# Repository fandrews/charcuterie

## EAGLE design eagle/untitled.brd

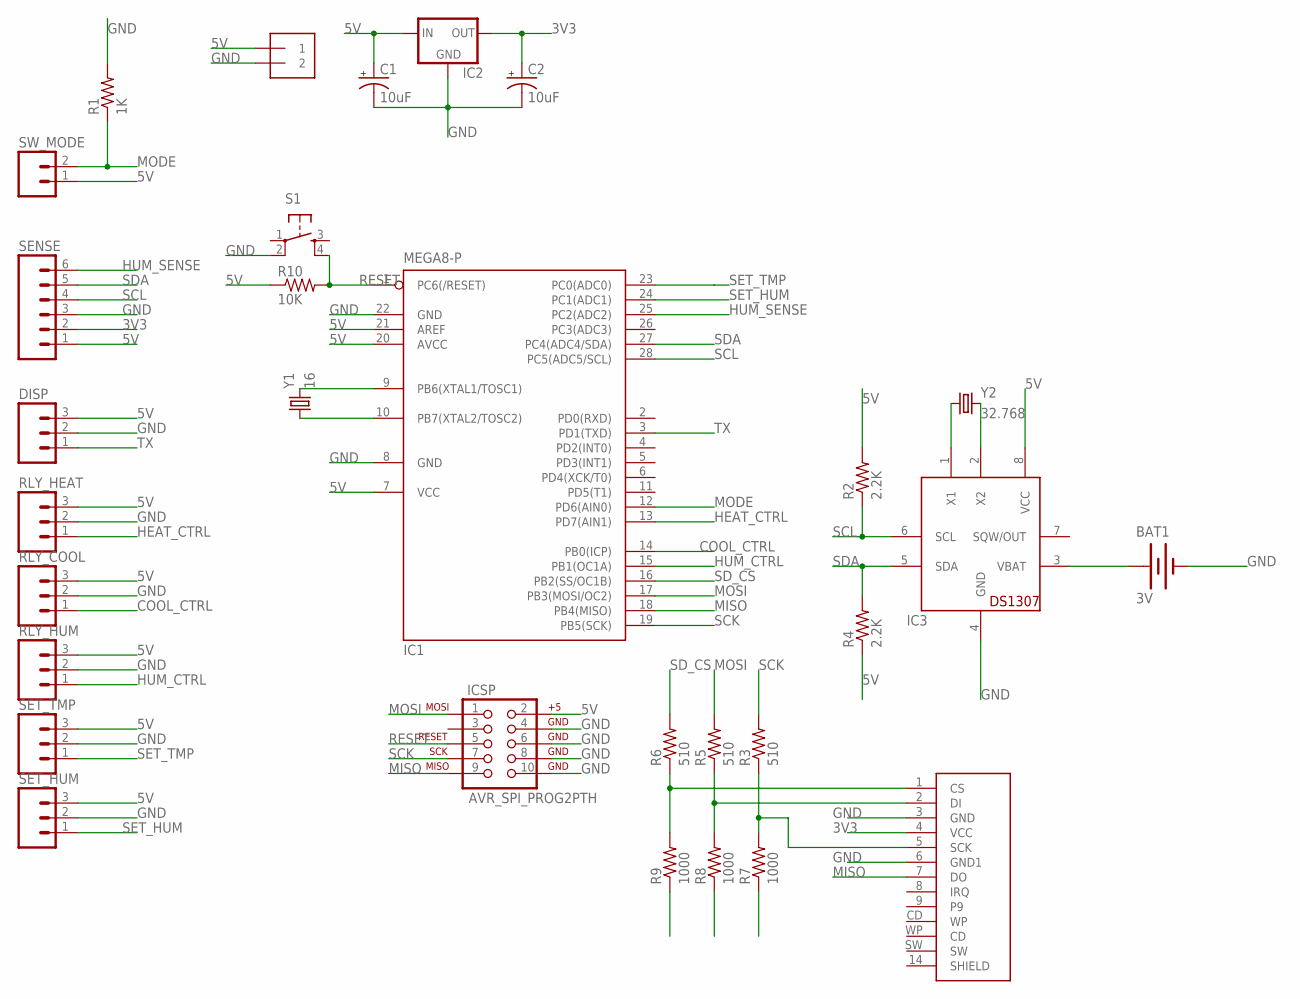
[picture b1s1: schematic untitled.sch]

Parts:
BAT1: 3V; BATTCOM_20MM_PTH
C1, C2: 10uF; CPOL-RADIAL-10UF-25V
DISP: M03PTH; 1X03
IC1: MEGA8-P; DIL28-3
IC2: V_REG_78XX-TO-220; TO-220-ALT
IC3: DS1307; DIL08
ICSP: AVR_SPI_PROG2PTH; AVR_ICSP
PWR_IN: 1X2-3.5MM
R1: 1K; AXIAL-0.3
R2, R4: 2.2K; AXIAL-0.3
R3, R5, R6: 510; AXIAL-0.3
R7, R8, R9: 1000; AXIAL-0.3
R10: 10K; AXIAL-0.3
RLY_COOL: M03PTH; 1X03
RLY_HEAT: M03PTH; 1X03
RLY_HUM: M03PTH; 1X03
S1: TAC_SWITCHPTH; TACTILE-PTH
SD_CARD: SD_CARD_SOCKETSD; SD-MMC_SOCKET-PP
SENSE: M06SIP; 1X06
SET_HUM: M03PTH; 1X03
SET_TMP: M03PTH; 1X03
SW_MODE: M02JST-PTH-2; JST-2-PTH
Y1: 16; HC49U-V
Y2: 32.768; TC26H

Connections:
3V3: C2.1 (+), IC2.OUT, SD_CARD.4 (VCC), SENSE.2
5V: C1.1 (+), DISP.3, IC1.7 (VCC), IC1.20 (AVCC), IC1.21 (AREF), IC2.IN, IC3.8 (VCC), ICSP.2, PWR_IN.1, R2.P$2 (2), R4.P$1 (1), R10.P$1 (1), RLY_COOL.3, RLY_HEAT.3, RLY_HUM.3, SENSE.1, SET_HUM.3, SET_TMP.3, SW_MODE.1
COOL_CTRL: IC1.14 (PB0(ICP)), RLY_COOL.1
GND: BAT1.2 (-), C1.2 (-), C2.2 (-), DISP.2, IC1.8 (GND), IC1.22 (GND), IC2.GND, IC3.4 (GND), ICSP.4, ICSP.6, ICSP.8, ICSP.10, PWR_IN.2, R1.P$2 (2), R7.P$1 (1), R8.P$1 (1), R9.P$1 (1), RLY_COOL.2, RLY_HEAT.2, RLY_HUM.2, S1.2, SD_CARD.3 (GND), SD_CARD.6 (GND1), SENSE.3, SET_HUM.2, SET_TMP.2
HEAT_CTRL: IC1.13 (PD7(AIN1)), RLY_HEAT.1
HUM_CTRL: IC1.15 (PB1(OC1A)), RLY_HUM.1
HUM_SENSE: IC1.25 (PC2(ADC2)), SENSE.6
MISO: IC1.18 (PB4(MISO)), ICSP.9, SD_CARD.7 (DO)
MODE: IC1.12 (PD6(AIN0)), R1.P$1 (1), SW_MODE.2
MOSI: IC1.17 (PB3(MOSI/OC2)), ICSP.1, R5.P$2 (2)
unnamed: IC1.9 (PB6(XTAL1/TOSC1)), Y1.2
unnamed: IC1.10 (PB7(XTAL2/TOSC2)), Y1.1
unnamed: IC3.1 (X1), Y2.1
unnamed: IC3.2 (X2), Y2.2
unnamed: BAT1.1 (+), IC3.3 (VBAT)
unnamed: R6.P$1 (1), R9.P$2 (2), SD_CARD.1 (CS)
unnamed: R5.P$1 (1), R8.P$2 (2), SD_CARD.2 (DI)
unnamed: R3.P$1 (1), R7.P$2 (2), SD_CARD.5 (SCK)
RESET: IC1.1 (PC6(/RESET)), ICSP.5, R10.P$2 (2), S1.4
SCK: IC1.19 (PB5(SCK)), ICSP.7, R3.P$2 (2)
SCL: IC1.28 (PC5(ADC5/SCL)), IC3.6 (SCL), R2.P$1 (1), SENSE.4
SDA: IC1.27 (PC4(ADC4/SDA)), IC3.5 (SDA), R4.P$2 (2), SENSE.5
SD_CS: IC1.16 (PB2(SS/OC1B)), R6.P$2 (2)
SET_HUM: IC1.24 (PC1(ADC1)), SET_HUM.1
SET_TMP: IC1.23 (PC0(ADC0)), SET_TMP.1
TX: DISP.1, IC1.3 (PD1(TXD))

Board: 2 copper layers, 30 parts (0 on the bottom side), 26 nets, no tracks yet.

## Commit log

2012-04-27 adding eagle files

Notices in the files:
parts and their libraries:
SparkFun-Connectors: Licensing: CC v3.0 Share-Alike You are welcome to use this library for commercial purposes.
